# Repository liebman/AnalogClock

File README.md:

# AnalogClock 2.X

Project to sync analog clocks to a few milliseconds using NTP for time synchronization. Details of operation can be found in this [blog post](https://blog.taboola.com/analog-clocks-ntp/)

[I2CAnalogClock](I2CAnalogClock) contains the code for the ATTiny85 as an I2C based Analog Clock controller.  I am now using [PlatformIO](https://platformio.org/) for development.

[SynchroClock](SynchroClock) contains the code for the ESP8266 module.   I am now using [PlatformIO](https://platformio.org/) for development.

[NTPTest](NTPTest) contains a framework for testing the NTP class in an accelerated manor on linux or MacOS saving days of waiting for results.

[eagle](eagle) contains the [Eagle](https://www.autodesk.com/products/eagle/overview) design files and the BOM.

## Features

* Automatic daylight saving time adjustments
* Clock position & configuration saved on power fail
* Low power consumption: approx. 0.25ma in early testing
* adjustable tick/adjust pulse width/duty cycle/delay should support most one second "tick" (non-sweep) clocks.
* NTP implementation computes drift and uses that to increase accuricy between NTP updates

## Configuration

   When the clock is initially powered on it creates a wifi captive portal.  It will show up in the list of available wifi networks as SynchroClockXXXXXXX (where the X’s are some number).  Configuration mode can be forced by holding down the reset button until the LED is turns on and stays on for at least 2 seconds then releasing it. NOTE that if you conrinue holding the reset button for more than 10 seconds the LED will go back off initiating a factory reset to default settings. When you connect to this you are given a menu that lets you set many configuration options:

* Wifi Network (SSID)
* Wifi Network password
* Clock Position - enter the current time shown on the clock as HH:MM:SS.
* NTP Server to sync with
* 1st time change as 6 fields (US/Pacific would be: 2 0 0 3 2 -25200 meaning the second Sunday in March at 2am we change to UTC-7 hours, and Israel: -1 0 -2 3 2 10800 meaning the Friday before the last Sunday of in March at 2am we change to UTC+3)
  * occurrence - 2 would be the second occurrence of the day of week specified, -1 would be the last one.
  * day of week - where 0 = Sunday
  * days offset - +|- days, used for "the Friday before the last Sunday"
  * month - where 1 = January
  * hour - where 0 = midnight
  * time offset - this is the offset in seconds from UTC
* 2nd time change as 5 fields as described above (US/Pacific: 1 0 0 11 2 -28800 meaning the first Sunday in November at 2am we change to UTC-8 hours, and Israel: -1 0 0 10 2 7200 meaning the last Sunday of October we change to UTC-2)

Advanced options:

* Stay Awake - when set true the ESP8266 will not use deep sleep and will run a small web servers allowing various operations to be performed with an http interface.
* Tick Pulse - this is the duration in milliseconds of the “tick”.
* Tick Duty Cycle - the percentage of time that the tick is on using PWM
* Adjust Start Pulse - this uis the duration in milliseconds of the initial pulse of an adjustment
* Adjust Pulse - this is the duration in milliseconds of the “tick” used to advance the clock rapidly.
* Adjust Duty Cycle - the percentage of time that the tick is on using PWM
* Adjust Delay - this is the delay in milliseconds between “ticks” when advancing the clock rapidly.
* Network Logger Host - (optional) hostname to send log lines to.
* Network Logger Port - (optional) tcp port to send log lines to.
* Clear NTP Persist - when set 'true' clears any saved adjustments and drift calculations.

## Schematic

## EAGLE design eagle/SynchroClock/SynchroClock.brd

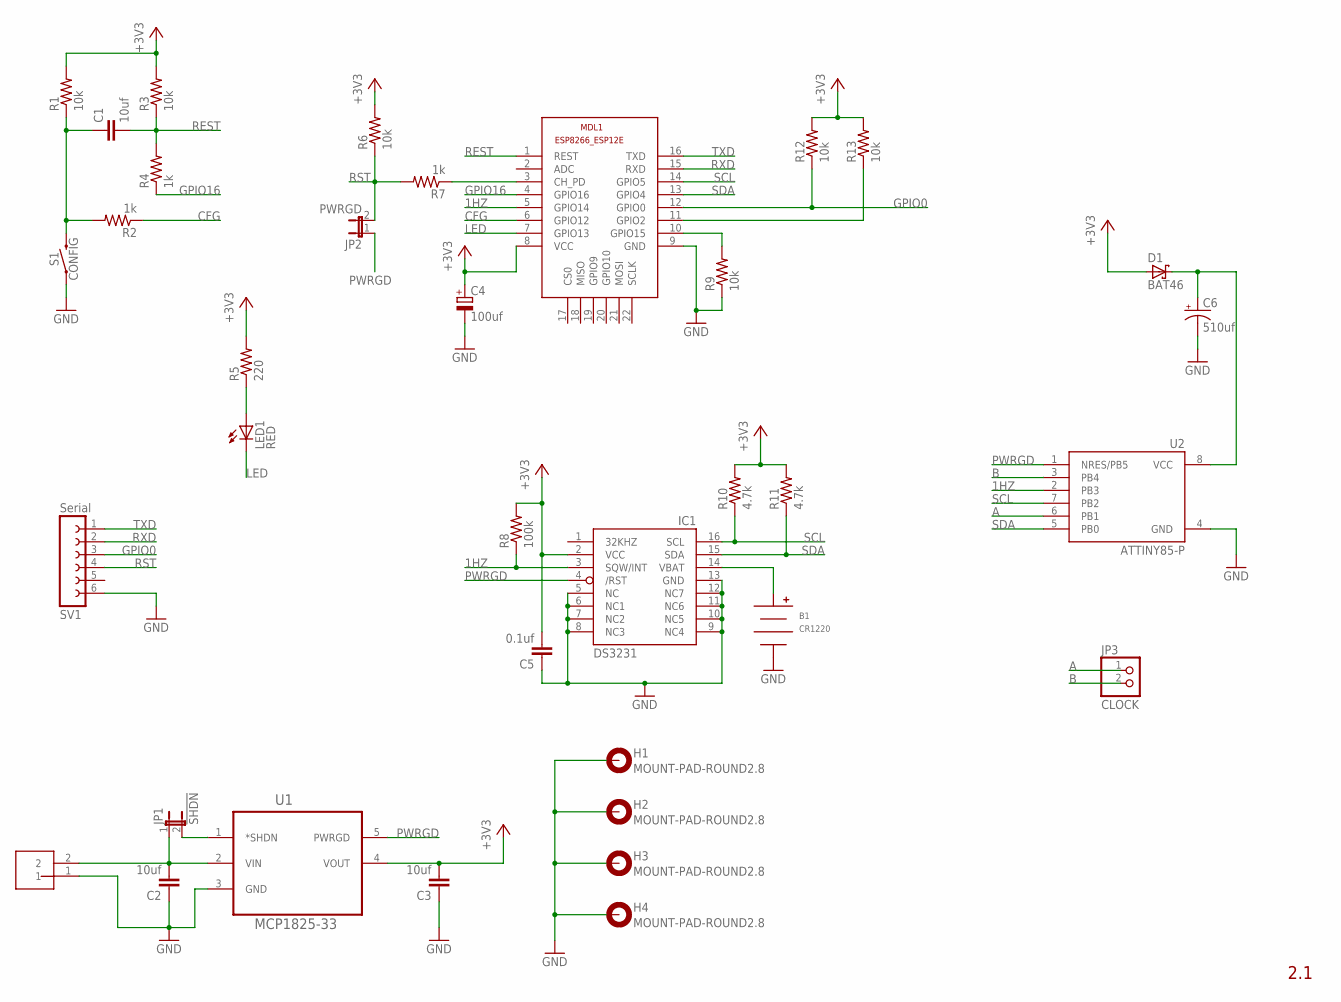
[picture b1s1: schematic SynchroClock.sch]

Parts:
B1: CR1220; HARWIN-CR1220
C1, C2, C3: 10uf; C5B2.5
C4: 100uf; E2,5-5
C5: 0.1uf; C2.5-2
C6: 510uf; E3,5-8
D1: BAT46; DO35-10
H1, H2, H3, H4: MOUNT-PAD-ROUND2.8; 2,8-PAD
IC1: DS3231/SO; SO16W
J1: VIN; 2_PIN_JST-XH
JP1: !SHDN; 1X02
JP2: PWRGD; 1X02
JP3: CLOCK; 1X02
LED1: RED; LED3MM
MDL1: ESP12E; ESP8266-ESP12E
R1, R3, R6, R9, R12, R13: 10k; 0204V
R2, R4, R7: 1k; 0204V
R5: 220; 0204V
R8: 100k; 0204V
R10, R11: 4.7k; 0204V
S1: CONFIG; TACTILE_SWITCH_PTH_6.0MM
SV1: Serial; FE06
U1: MCP1825-33; TO170P482X1024X3124-5P
U2: ATTINY85-P; PDIP08_300MIL

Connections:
1HZ: IC1.3 (SQW/INT), MDL1.5 (GPIO14), R8.1, U2.2 (PB3)
!SHDN: JP1.2, U1.1 (*SHDN)
+3V3: C3.2, C4.+, C5.2, D1.A, IC1.2 (VCC), MDL1.8 (VCC), R1.2, R3.2, R5.2, R6.2, R8.2, R10.2, R11.2, R12.2, R13.2, U1.4 (VOUT)
+5V: C2.2, J1.2, JP1.1, U1.2 (VIN)
A: JP3.1, U2.6 (PB1)
ATVCC: C6.+, D1.C, U2.8 (VCC)
B: JP3.2, U2.3 (PB4)
CFG: MDL1.6 (GPIO12), R2.1
CH_PD: MDL1.3 (CH_PD), R7.1
GND: B1.NEG, C2.1, C3.1, C4.-, C5.1, C6.-, H1.B2,8, H2.B2,8, H3.B2,8, H4.B2,8, IC1.5 (NC), IC1.6 (NC1), IC1.7 (NC2), IC1.8 (NC3), IC1.9 (NC4), IC1.10 (NC5), IC1.11 (NC6), IC1.12 (NC7), IC1.13 (GND), J1.1, MDL1.9 (GND), R9.1, S1.1, SV1.6, U1.3 (GND), U2.4 (GND)
GPIO0: MDL1.12 (GPIO0), R12.1, SV1.3
GPIO2: MDL1.11 (GPIO2), R13.1
GPIO15: MDL1.10 (GPIO15), R9.2
GPIO16: MDL1.4 (GPIO16), R4.1
LED: LED1.K (C), MDL1.7 (GPIO13)
unnamed: C1.1, R1.1, R2.2, S1.3 (2)
unnamed: LED1.A, R5.1
PWRGD: IC1.4 (/RST), JP2.1, U1.5 (PWRGD), U2.1 (NRES/PB5)
REST: C1.2, MDL1.1 (REST), R3.1, R4.2
RST: JP2.2, R6.1, R7.2, SV1.4
RXD: MDL1.15 (RXD), SV1.2
SCL: IC1.16 (SCL), MDL1.14 (GPIO5), R10.1, U2.7 (PB2)
SDA: IC1.15 (SDA), MDL1.13 (GPIO4), R11.1, U2.5 (PB0)
TXD: MDL1.16 (TXD), SV1.1
VBAT: B1.POS, IC1.14 (VBAT)

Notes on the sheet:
2.1

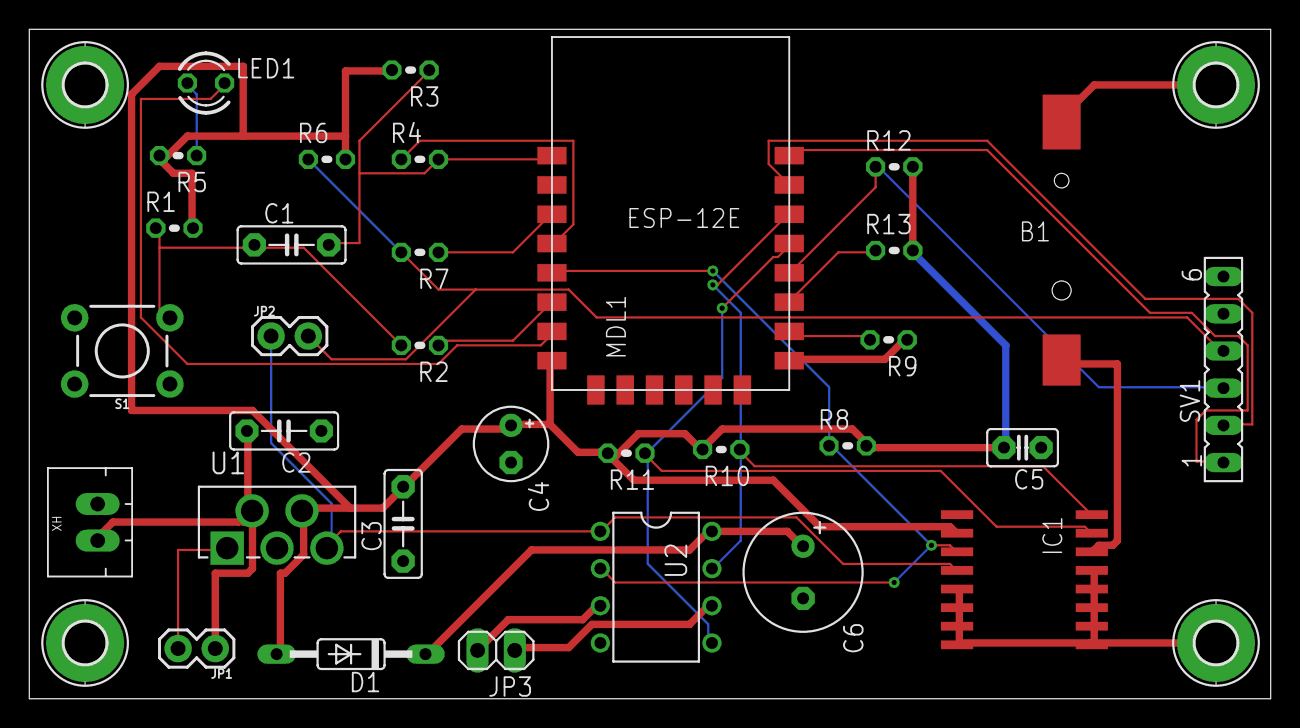
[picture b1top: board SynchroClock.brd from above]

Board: 2 copper layers, 84.8 x 45.7 mm, 36 parts (0 on the bottom side), 25 nets.

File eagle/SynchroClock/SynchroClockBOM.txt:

Partlist exported from /Users/liebman/src/AnalogClock/eagle/SynchroClock/SynchroClock.sch at 10/7/17 9:38 AM

Part Value              Device                          Package                  Description                                             
B1   CR1220             CR1220-HOLDER                   HARWIN-CR1220                                                                    
C1   10uf               C5/2.5                          C5B2.5                   CAPACITOR                                               
C2   10uf               C5/2.5                          C5B2.5                   CAPACITOR                                               
C3   10uf               C5/2.5                          C5B2.5                   CAPACITOR                                               
C4   100uf              CPOL-EUE2.5-5                   E2,5-5                   POLARIZED CAPACITOR, European symbol                    
C5   0.1uf              C2.5/2                          C2.5-2                   CAPACITOR                                               
C6   510uf              CPOL-USE3.5-8                   E3,5-8                   POLARIZED CAPACITOR, American symbol                    
D1   BAT46              BAT46                           DO35-10                  Schottky Diode                                          
H1   MOUNT-PAD-ROUND2.8 MOUNT-PAD-ROUND2.8              2,8-PAD                  MOUNTING PAD, round                                     
H2   MOUNT-PAD-ROUND2.8 MOUNT-PAD-ROUND2.8              2,8-PAD                  MOUNTING PAD, round                                     
H3   MOUNT-PAD-ROUND2.8 MOUNT-PAD-ROUND2.8              2,8-PAD                  MOUNTING PAD, round                                     
H4   MOUNT-PAD-ROUND2.8 MOUNT-PAD-ROUND2.8              2,8-PAD                  MOUNTING PAD, round                                     
IC1  DS3231/SO          DS3231/SO                       SO16W                                                                            
J1   VIN                2_PIN_JST-XH                    2_PIN_JST-XH             Corrected for XH 2 pin                                  
JP1  !SHDN              JUMPER-2PTH                     1X02                     Jumper                                                  
JP2  PWRGD              JUMPER-2PTH                     1X02                     Jumper                                                  
JP3  CLOCK              PINHD-1X2                       1X02                     PIN HEADER                                              
LED1 RED                LED3MM                          LED3MM                   LED                                                     
MDL1 ESP12E             ESP8266-12EESP8266-ESP12E       ESP8266-ESP12E           ESP8266-12E with additional I/O and GPIO04/05 corrected 
R1   10k                R-US_0204/2V                    0204V                    RESISTOR, American symbol                               
R2   1k                 R-US_0204/2V                    0204V                    RESISTOR, American symbol                               
R3   10k                R-US_0204/2V                    0204V                    RESISTOR, American symbol                               
R4   1k                 R-US_0204/2V                    0204V                    RESISTOR, American symbol                               
R5   220                R-US_0204/2V                    0204V                    RESISTOR, American symbol                               
R6   10k                R-US_0204/2V                    0204V                    RESISTOR, American symbol                               
R7   1k                 R-US_0204/2V                    0204V                    RESISTOR, American symbol                               
R8   100k               R-US_0204/2V                    0204V                    RESISTOR, American symbol                               
R9   10k                R-US_0204/2V                    0204V                    RESISTOR, American symbol                               
R10  4.7k               R-US_0204/2V                    0204V                    RESISTOR, American symbol                               
R11  4.7k               R-US_0204/2V                    0204V                    RESISTOR, American symbol                               
R12  10k                R-US_0204/2V                    0204V                    RESISTOR, American symbol                               
R13  10k                R-US_0204/2V                    0204V                    RESISTOR, American symbol                               
S1   CONFIG             MOMENTARY-SWITCH-SPST-PTH-6.0MM TACTILE_SWITCH_PTH_6.0MM Momentary Switch (Pushbutton) - SPST                    
SV1  Serial             FE06-1                          FE06                     FEMALE HEADER                                           
U1   MCP1825-33         MCP1825-3302E/AT                TO170P482X1024X3124-5P   IC, LDO, ADJ, 500MA                                     
U2   ATTINY85-P         ATTINY85-P                      PDIP08_300MIL            ATMEL ATtiny 85

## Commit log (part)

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2017-03-23 Added start of schematic (its going to change a lot!)
2017-03-23 using atmega328 for now
2017-03-23 added eclipse project settings
2017-03-25 added conditionals for ATtiny85
2017-03-25 more tuning, added in/out of position as HH:MM:SS
2017-03-25 use interrupt timers for ticks conditional on #define USE_TIMER
2017-03-25 always use timer/interrupts, remove USE_TIMER conditionals
2017-03-25 reduce delay/duration sizes to 8bit unsigned
2017-03-26 disable serial debug messages
2017-03-26 allow specifing noon/midnight as 12:00:00 instead of 00:00:00
2017-03-26 update schematic (WIP)
2017-03-26 refactor - move clock interface to seperate class
2017-03-26 added diodes to drop clock output voltage
2017-03-26 fixed origin timestamp, attempted to compute delay and offset (not working)
2017-03-26 more schematic work
2017-03-29 use 1.5v to drive clock - better timing 16ms tick pusles and an adjust delay of 8ms
2017-03-30 fix overflows
2017-03-31 compute NTP offset correctly
2017-03-31 use offset to set time, create dbug print macros instead of Serial.print*
2017-03-31 cleanup, make messages optional
2017-04-19 Fleshout circuit more
2017-04-20 v1 PCB layout
2017-04-23 lock in v0.1 kicad
2017-04-25 add interrupt/timer config for ATTiny85
2017-04-29 ATTiny85 - working sort of.... i2c hangs on first request after a write
2017-04-30 Cleanup - no longer need wire library wrapper since USIWire is compatable!
2017-04-30 Use sleep to reduce power
2017-05-02 improved NTP
2017-05-07 update default adjust delay to 12ms, up from 8ms
2017-05-07 added factory restart support and saving config values in EEPROM
2017-05-08 decrement right after check - not after delays!
2017-05-08 added config saved to EEPROM (only timezone offset for now)
2017-05-11 added more config options (limit to 10 without hacking the WifiManager lib!)
2017-05-11 added old version new version updated a bit - still not done or compleatly tested
2017-05-12 remove eclipse project settings
2017-05-13 Fixed race conditions with position and adjustment value during adjustment
2017-05-13 added sleep_delay to sleep DRV8838 to save power.
2017-05-14 added config for DRV sleep delay
2017-05-14 use timer (not loop) for adjustment, now both tick and adjust are interrupt/timer driven always fire one tick on startup to sync clock motor
2017-05-14 format cleanup
2017-05-14 use idle sleep for now (working on power down sleep)
2017-05-15 now power down the DRV8838 and the I2CAnalogClock MCU to save power (from 2.6ma+ to 0.74ma avg!!!) Converted the ATTiny85 reset pin to an output as I needed a pin for teh DRV disable!
2017-05-15 updated with reset & sleep changes
2017-05-26 new implementation to talk with DS3231 w/wire error checking added some wire error checking to Clock I2C bus Recovery method added via WireUtils
2017-05-26 added error codes for netRTCfromNTP()
2017-05-27 stability improvements and cleanup
2017-05-31 added mode debug states
2017-05-31 cleanup warning
2017-05-31 added Logger to hadle both Serial & network logging
2017-06-01 clean up unused code detect bad DateTime objects if readtime succedded but gave bad data
2017-06-01 declare vsnprintf as its not covered in any includes :-(
2017-06-04 If we wake with the reset button pressed and sleep_delay_left then the radio is off, use a deepSleep to turn it back on.
2017-06-04 added comment about short deep sleep
2017-06-04 use updated WiFiManager to allow more params
2017-06-04 adjust defaults, cleanup field sizes
2017-06-06 make sure newline is sent to TCP!
2017-06-07 created ConfigParam to clean up wifi config param code moved TZUtils into new TimeUtils that has many time related static methods
2017-06-07 handle negitive values for weel specification to indicate last, second to last etc
2017-06-07 added config params for 2 time changes to adn from DST
2017-06-15 compute a long double version of offset so we can easialy check abs value for when to set RTC
2017-06-17 use median of last values if ntp offset comes back as >900ms
2017-06-17 stop the clock for up to 60 seconds to handle negative delta when setting from RTC
2017-06-20 use 64bit ints for offset cleanup median code
2017-06-27 Apply license
2017-06-27 switch to eagle cad for hardware
2017-06-28 fixed the network logger port configuration
2017-07-03 Add a TCP connect timeout and max connect attemps till we bail on TCP and stick with serial only.
2017-07-03 Last commit before removal
2017-07-03 Use new NTP Class
2017-07-04 Persist servername and ip address, use persisted ip address if server name remains unchanged. TBD lookup server address again if reachability is bad.
2017-07-04 improve NTP accuracy
2017-07-06 Switch offset to double, jitter calculations for observation.
2017-07-14 consolidate Logger #defines
2017-07-14 major refactor of NTP code, now includes NTPTest framework to allow NTP debugging on MacOS/unix
2017-07-15 added a debug hack to hard code the WiFi info added some formatting
2017-07-19 correct the mdelay calculation for negative offsets
2017-07-19 disable DS3231 debug
2017-07-19 switch to 1.5v for clock voltage regulator
2017-07-23 updated NTP calculations
2017-07-25 improved poll interval calculation based on our trust of the drift value
2017-07-25 minor comment update
2017-07-25 Updated NTP algo with drift. Still need to find a way to speed up initial sync and drift calculation.
2017-07-26 updated algo
2017-07-28 Improvements on ntp poll interval - still work in progress
2017-07-28 more poll interval testing/improvements
2017-07-29 tune threshold from 40ms to 20ms to compute drift faster
2017-07-30 added schematic image
2017-09-01 Code now works with basic h bridge, now need to update the schematic/board
2017-09-09 no longer have to use stay awake logic, timeing still not right for AP duration/delay/duty
2017-09-09 "development" version - board that does not have the clock driver
2017-09-12 correctly apply current clock settings if its running over the config, if its not running then the config wins
2017-09-12 removed un-needed non-PWM & DRV code
2017-09-12 cleanup to remove un-needed sleep delay as it was only used for the DRV motor controler
2017-09-13 minor cleanup / set current defaults in I2CAnalogClock
2017-09-16 Updated for v2
    Now uses PWM for ticks (saves power)
    No longer using motor controller (also saves power)
2017-09-16 add version
2017-09-16 updated schematic for current Alpha version
2017-09-17 no real changes
2017-09-17 basic powerfail now works - still need to add more data to be saved
2017-09-17 added power fail circuit for ATtiny85 added BOM save all clock properties at power fail
2017-09-18 updated schematic
2017-09-21 document attiny8 fuse settings set register with PWM_TOP so it can be changed
2017-09-24 added powerfail detection and saving of clock position and state (tick or tock & enababled or not) I2CAnalogClock (ATtiny) now has its config saved
2017-10-02 remove 4mhz option + small cleanups
2017-10-02 cleanup clock save config command added default log address/port (need to disable before production ready) remove clock timeing settings from config as they are saved on the ATtiny85 added defined de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
2017-10-07 board version 2.1
2017-10-07 board 2.1a
2017-10-08 updated schematic for readme
2017-10-21 cleaup readme a bit
2017-10-22 Apply potential timezone changes after adjusting RTC.
2017-10-23 Sometimes the RTC is not readable, retry when that happens during set rtc from offset
2017-10-26 Fixes #7
2017-10-26 initial refactor - debug enabled #6
2017-10-26 Implememnted "days offset" (#6)
2017-10-26 use updated version of my WiFiManager changes to allow more than 10 params.
2017-10-26 disable WiFiManager debug messages
2018-03-21 added timezone info use actual pin numbers so we can use generic board
2018-03-22 try running travis
2018-03-22 fixes
2018-03-22 try travis
2018-03-22 fix "case" typo Dlog.h -> DLog.h
2018-03-22 add PinChangeInterrupt lib
2018-03-22 added travis build image
2018-03-22 dynamically allocate wifi params
2018-03-24 A bit of cleanup
2018-03-24 enable clock on OTA success if it was enabled before OTA started
2018-03-25 Implement factory reset - resolves #10 Disable config ports in autoConnect - resolves #11
    Requires: https://github.com/tzapu/WiFiManager/pull/575
2018-03-25 need branch pf WiFiManager to build for now
2018-03-25 SynchroClock works with platformio
2018-03-27 factory reset was very broken. Now working!
2018-03-28 use getEdgeSyncedTime to get time synched to second start (with retries)
2018-03-28 use development version of WiFiManager
2018-03-28 include time.h headers
2018-03-28 added logging connection timeout/max attempts improve logging of chip id and versions
2018-04-03 attempt with platformio
2018-04-03 try sudo
2018-04-03 no update
2018-04-03 testing travis config
2018-04-03 Build with platformio (#12)
    Include platformio builds as part of CI. This is a first step to adding release generation from travis builds.
2018-04-05 use a modified fork of the arduino platformio framework to get updated ATTiny support
2018-04-05 change log prefix to seconds since boot + chip ID
2018-04-06 added submodules so we controle the versions
2018-04-06 build attempt using submodules
2018-04-06 fix hardware folder for arduino build on travis
2018-04-06 move esp8266 hardware to be more arduino like
2018-04-06 correct platform spec for esp
2018-04-06 remove last vestages of platformio
2018-04-06 Drop platformio and use submodules to load hardware and libraries from git (#13)
    * added submodules so we controle the versions
    * remove platformio
2018-04-20 hold button for 1 second for config mode, 10 more seconds for factory reset
2018-04-28 Backlink to CADLAB.io has been added.
2018-06-17 added syslg & cleanup SSID/Device name
2018-07-22 update to most recient working WifiManager
2018-08-12 updated WiFiManager & core
2018-08-18 updated WiFiManager
2018-08-18 update WiFiManager again
2018-08-18 update esp8266 core
2018-12-21 fix submodule
2018-12-21 adjust esp8266 device settings for updated core
2018-12-21 adjust esp8266 device settings for updated core some more
2019-07-16 switch to platformIO
2019-07-16 fix travis
2019-07-16 update readme for platformio & reset changes
2019-07-24 add platformio fuse setting and correct cpu freq for attiny85
2019-07-28 add workaround to prevent flash erase when using the platformio fuses target
2019-08-25 set default timechange settings from platformio.ini via build_flags
2019-08-25 fix issues with python3
2019-08-25 Support a local.init to add private extensions to platformio.init
2019-08-25 sync clock with RTC when WiFi connect fails in case of power outage where WiFi is not available
2019-08-25 Add include and test directories for future use and because platformio init creates them even with an existing project.
2019-08-30 started unit tests (its a work in progress) moved many file to include & lib for easy access from unit tests broke pin definitions out into a seperate include file for easy access from tests
2019-09-06 - increase CLOCK_STRETCH_LIMIT - bump SynchroClock version to 1.1.6 - define NTP_REQUEST_COUNT in platformio.ini for >1 NTP req's per cycle when more than one NTP choose the lowest delay - fix warnin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
2019-09-08 set drift_timestamp usint EPOCH not NTP timestamp
2019-09-08 fix poll interval calculation in getPollInterval() update version to 1.1.8
2019-09-09 improve selection of samples for drift estimate by using same criteria as for selecting offisets to use. version 1.1.9
2019-09-14 include pio env name in version string timestamps in samples now reflects new time and not time before offset adjustment don't include the initial first sample offset in estimated drift calculation S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
2019-09-18 bump version to 1.1.11 print current time (GMT) with timestamps 10 samples first sample set in 4 hours
2019-09-23 added a few comments and small debug fix
2019-09-25 only compute drift if we have at least 4 valid intervals bump version to 1.1.12
2021-09-08 Update to Espressif8266 2.6.3 toolchain
    This necessitates the removal (temporarily, at least) of -Werror so we
    can complete a compilation successfully.
2021-09-08 Use GitHub Actions
    Since my balance went negative on Travis-CI, it has never built anything for me.
    Switch to GitHub Actions which works arguably better than Travis.
2021-09-08 GitHub Actions: remove staging env
    The staging environment does not work, so remove it from CI for now.
2021-09-08 Update the repo to more modern toolchain (#21)
    * Update to Espressif8266 2.6.3 toolchain
    This necessitates the removal (temporarily, at least) of -Werror so we
    can complete a compilation successfully.
    * Update mkdata.py for Python 3
    Python 2.7 has been sunsetted since January 1, 2020. Update the builder
    to use Python 3.9 as it is the latest stable version.

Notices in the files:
parts and their libraries:
SparkFun-Switches: Licensing: Creative Commons ShareAlike 4.0 International - https://creativecommons.org/licenses/by-sa/4.0
